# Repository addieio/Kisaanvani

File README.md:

<div align="center">

# 🌾 किसानवाणी (KisanVaani)
### *Voice-First AI Agronomist, ESP32-C6 Soil Telemetry Stake & Mandi-Direct Escrow Portal*
#### **Built for Hack with Delhi 4.0**

**Empowering smallholder Indian farmers through biophysical root-zone telemetry, edge computer-vision crop pathology, Indic-language voice AI, offline GSM feature-phone inclusion, and disintermediated fair-price mandi sales.**

---

### 🌐 Live Production Deployment
**Web Platform & Escrow Marketplace**: **[https://kisanvaani-eight.vercel.app](https://kisanvaani-eight.vercel.app)**
*Experience the live Farmer Portal, B2B Procurement Desk, Cold-Chain Logistics Calculator, and Government Sowing Quota Balancer directly in your browser.*

---

</div>

## 📖 Executive Summary & Vision

Smallholder cultivators across India face four systemic vulnerabilities:
1. **Late Crop Disease Detection**: Delayed pathology identification causes 20–40% preventable yield loss from foliar blights, rusts, and root rot.
2. **The Smartphone & Connectivity Divide**: Over 65% of rural Indian farmers do not own smartphones or operate in rural connectivity dark zones. They carry basic ₹1,000 keypad feature phones (GSM/2G) and are excluded from modern touch-screen apps.
3. **Digital Literacy & Interface Barriers**: Text-heavy dashboards alienate non-literate farmers who operate predominantly through verbal communication.
4. **Exploitative Middlemen & Credit Inaccessibility**: Middlemen depress farmgate prices, while banks (KCC loans) and insurers (PMFBY claims) require verified, tamper-proof soil and crop telemetry that farmers cannot produce.

**KisanVaani unifies five complementary engineering pillars to solve these challenges end-to-end:**
- 📡 **Real IoT Hardware Stake (Seeed Studio XIAO ESP32-C6)**: Field telemetry with Nordic UART BLE 5.0, Crowtail capacitive moisture auto-calibration, DHT22 micro-climate monitoring, MPU-6050 physical tilt detection, SSD1306 OLED with 5-second alert toasts, and Active-LOW pump relay safety cutoffs.
- 📞 **Zero-Smartphone Offline Telephony (Twilio Voice IVR + Sarvam AI Bulbul TTS)**: Enables farmers with basic keypad feature phones to verbally list crops, accept buyer bids via automated Hindi phone calls, and receive soil emergency alerts via SMS.
- 📱 **Voice-First Mobile App (Flutter & Apple iOS 18 Design)**: Large touch targets (≥74px), zero typing, 5 regional languages (Hindi, Punjabi, Marathi, Tamil, English), reactive BLE scanner, and tactile haptic feedback.
- 🔬 **Edge Computer Vision & AI Agronomist (YOLOv8 + Google Gemini 3.8 Flash)**: Custom-trained 12-class edge pathology model paired with conversational Hindi agronomy advice and spoken audio.
- 🌐 **Full-Stack Web Platform & Escrow Marketplace (Next.js 15 & Supabase on Vercel)**: Farmer portal, B2B restaurant procurement portal with radial cold-chain logistics, government district sowing quota balancer, and certified KCC/PMFBY financial passport exports.

---

## 🏛️ System Architecture

```
                                    [ Farmer / Cultivator ]
                                               │
                ┌───────────────────────────────┼───────────────────────────────┐
                ▼                               ▼                               ▼
      [ Next.js 15 Web PWA ]         [ 2G Basic Feature Phone ]         [ Flutter Android App ]
  https://kisanvaani-eight.vercel.app  (Zero Internet / Keypad GSM)      (BLE 5.0, Camera HUD, TTS)
                │                               │                               │
                │                ┌──────────────┴──────────────┐                │
                │                ▼                             ▼                │
                │      [ Twilio Voice IVR ]          [ Twilio SMS Gateway ]     │
                │   • Verbal Crop Posting (NLU)     • 4-Digit Handover Gate PIN │
                │   • Sarvam Bulbul Indic TTS       • Biophysical Soil Alarms   │
                │   • DTMF / Voice Bid Acceptance   (Hypoxia, Drought, Urea)    │
                │                └──────────────┬──────────────┘                │
                │                               │                               │
                ├───────────────────────────────┼───────────────────────────────┤
                ▼                               ▼                               ▼
    [ YOLOv8 Edge Vision ]           [ Gemini 3.8 Flash Doctor ]       [ XIAO ESP32-C6 Stake ]
    • Custom 12-Class Model          • Actionable Hindi Advice         • Crowtail Capacitive Moist
    • Trained Weights (best.pt)      • Automated Speech Generation     • DHT22 Temp & Humidity
    • Bounding Box Localization      • Voice Triage Dialog             • MPU-6050 6-DOF Tilt IMU
                │                               │                      • SSD1306 0.96" OLED Toast
                │                               │                      • Dual Active-LOW Relay Cutoff
                │                               │                               │
                └───────────────────────────────┴───────────────────────────────┘
                                                │
                                                ▼
                                [ Supabase PostgreSQL 16 ]
                       • 16 Normalized Database Tables
                       • Regional Sowing Quota Locks (Anti-Glut)
                       • Mandi-Direct Escrow (4-Digit PIN Handover)
                       • KCC Loan & PMFBY Insurance Dossier Exports
```

---

## 📡 Hardware Stake & Sensor Architecture

The physical field sensor stake monitors root-zone metrics, micro-climate factors, and physical stake stability, communicating over Nordic UART BLE 5.0:

```
                  ┌─────────────────────────────────────────────────────────┐
                  │              Seeed Studio XIAO ESP32-C6                 │
                  │             (RISC-V 160MHz, BLE 5.0, Wi-Fi 6)           │
                  └──────┬────────────┬───────────┬────────────┬────────────┘
                         │            │           │            │
            Analog ADC1  │   1-Wire   │    I2C    │    GPIO    │ Dual GPIO
               (D1/GPIO1)│  (D2/GPIO2)│ (D4/D5)   │ (D8/GPIO19)│ (D9/GPIO20 & D10/GPIO9)
                         ▼            ▼           ▼            ▼            ▼
                  ┌────────────┐ ┌─────────┐ ┌─────────┐ ┌──────────┐ ┌────────────────┐
                  │  Crowtail  │ │  DHT22  │ │ SSD1306 │ │Active-Low│ │Optocoupled Dual│
                  │ Capacitive │ │Temp/Hum │ │  OLED   │ │  Buzzer  │ │Relay Motor Cut │
                  │  Moisture  │ │ Sensor  │ │ Display │ │(Acoustic)│ │ (Songle 10A)   │
                  └────────────┘ └─────────┘ └────┬────┘ └──────────┘ └────────────────┘
                                                  │
                                                  ▼
                                             ┌─────────┐
                                             │MPU-6050 │
                                             │6-DOF IMU│
                                             │ (Tilt)  │
                                             └─────────┘
```

### 1. What All Sensors Are There & How Each Works

#### 🌾 A. Crowtail Capacitive Soil Moisture Sensor (v2.0)
* **Hardware Interfacing**: Analog Pin `D1` / `GPIO 1` (`ADC1_CH1`).
* **Working Principle**: Operates on the principle of **dielectric permittivity** of soil. Unlike cheap resistive probes that corrode rapidly through electrolysis, the capacitive design uses insulated copper traces on a PCB forming a capacitor whose dielectric medium is the surrounding soil and moisture. Water has a high dielectric constant ($\approx 80$) compared to dry soil ($\approx 3\text{--}5$) and air ($\approx 1$).
* **Signal Processing & Auto-Calibration**: As volumetric water content rises, capacitance increases, lowering the timer output voltage. The firmware captures 12-bit ADC values ($0\text{--}4095$) with multi-sample rolling average smoothing, dynamically calibrating the dry-air baseline ($\approx 2800\text{--}3100$ raw ADC) and saturation threshold ($\approx 1200\text{--}1400$ raw ADC) into a calibrated $0\text{--}100\%$ Volumetric Soil Moisture metric.
* **Root Hypoxia Emergency Action**: When moisture exceeds $80\%$ (waterlogging / anaerobic root suffocation danger), the stake triggers an instant hardware pump cutoff, emits acoustic siren pulses, and flashes an OLED alert.

#### 🌡️ B. DHT22 (AM2302) Digital Temperature & Relative Humidity Sensor
* **Hardware Interfacing**: Digital Pin `D2` / `GPIO 2` with an external $10\text{ k}\Omega$ pull-up resistor to $3.3\text{V}$.
* **Working Principle**: Uses a capacitive humidity sensing element and a high-precision Negative Temperature Coefficient (NTC) thermistor. An onboard 8-bit chip outputs calibrated digital signals over a proprietary single-bus 1-wire protocol.
* **Biophysical Role & Vapor Pressure Deficit (VPD)**: Accurately tracks micro-climate conditions around the crop canopy ($-40^\circ\text{C}$ to $+80^\circ\text{C} \pm 0.5^\circ\text{C}$; $0\text{--}100\%$ RH $\pm 2\%$). Combined temperature and relative humidity allow real-time computation of **Vapor Pressure Deficit (VPD)**. When humidity remains $>90\%$ in warm temperatures, the biophysical engine predicts fungal spore germination (e.g., powdery mildew, leaf spot) before physical symptoms appear on leaves.

#### 📐 C. MPU-6050 6-Axis Motion Tracking Sensor (Accelerometer + Gyroscope)
* **Hardware Interfacing**: I2C Bus via `GPIO 22` (`SDA` / `D4`) and `GPIO 23` (`SCL` / `D5`) at $400\text{kHz}$ Fast Mode (I2C address `0x68`).
* **Working Principle**: Integrates a 3-axis MEMS accelerometer with a 3-axis MEMS gyroscope and an internal Digital Motion Processor (DMP).
* **Physical Telemetry Role**: Continuously monitors the physical inclination and spatial orientation of the field sensor stake. Detects physical displacement, stake toppling by high winds, heavy rain soil washouts, or cattle disturbances. If inclination exceeds $25^\circ$ from the vertical normal, the firmware flags a `STAKE_DISPLACED` status to alert the farmer that root-zone readings may no longer be accurate.

#### 📺 D. 0.96" SSD1306 Monochrome OLED Display (128x64 Pixels)
* **Hardware Interfacing**: Shared I2C Bus (`GPIO 22` SDA, `GPIO 23` SCL, I2C address `0x3C`).
* **Working Principle**: High-contrast self-emissive organic light-emitting diode matrix with zero backlight bleed, readable under harsh direct sunlight in the field.
* **Visual Layout & Toast Alert System**:
  - **Telemetry Carousel**: Cycles between real-time moisture %, temperature, humidity, NPK status, and pump relay states.
  - **Custom Compact Hindi Bitmaps**: Displays native Hindi text and icons (*नमी*, *मौसम*, *सिंचाई*, *उचित*, *सूखी*) without requiring external font flash overhead.
  - **5-Second Double-Border Toast System**: When app sliders or remote simulation commands are dispatched, an interruptible double-bordered alert card overrides the screen for exactly $5,000\text{ms}$ with beep tones, showing the updated parameter before restoring live metrics.

#### 🔊 E. Active-Low Acoustic Electromagnetic Buzzer (12mm)
* **Hardware Interfacing**: Digital Pin `D8` / `GPIO 19`.
* **Working Principle**: Built-in oscillation circuit driven by a low-side NPN/MOSFET switch. Pulling `GPIO 19` `LOW` activates the internal oscillator, driving the diaphragm at $\approx 2.7\text{kHz}$.
* **Acoustic Feedback Modes**: Provides distinct auditory feedback for rural field conditions: single short chirp ($100\text{ms}$) for button click / BLE command reception; triple rapid pulse ($3\times 80\text{ms}$) for threshold warnings; continuous pulsed siren for emergency over-irrigation pump cutoff.

#### ⚡ F. Dual-Pin Optocoupled Active-LOW Power Relay (Songle SRD-05VDC-SL-C)
* **Hardware Interfacing**: Driven in parallel by Digital Pin `D9` / `GPIO 20` (Primary) and Digital Pin `D10` / `GPIO 9` (Secondary) for pin fault tolerance and high switching reliability.
* **Working Principle**: Employs an EL817 optocoupler for complete galvanic isolation between the low-voltage ESP32 logic rail ($3.3\text{V}$) and high-power motor/pump circuits (up to $250\text{V AC} / 10\text{A}$ or $30\text{V DC} / 10\text{A}$). Pulling the control pins `LOW` illuminates the internal infrared LED, saturating the phototransistor and energizing the $5\text{V}$ relay coil.
* **Fail-Safe Protection**: Defaults to `HIGH` (Normally Open / de-energized) on reboot, power brownout, or high moisture ($>80\%$) to prevent field flooding.

---

### 2. Complete Hardware Circuit & Pinout Table

| Component | XIAO ESP32-C6 Pin | GPIO | Protocol / Mode | Connection Details |
| :--- | :--- | :--- | :--- | :--- |
| **Relay Signal (IN)** | **D9** *(Primary)* | **GPIO 20** | Digital Output | Active-LOW ($0\text{V}$ activates coil, turns motor ON) |
| **Relay Signal (ALT)** | **D10** *(Secondary)* | **GPIO 9** | Digital Output | Driven in parallel with D9 for pin fault tolerance |
| **Relay VCC** | **5V** | 5V Rail | Power | Connect to 5V rail (USB / external supply) |
| **Relay GND** | **GND** | GND | Ground | Common ground rail |
| **SSD1306 OLED SDA** | **D4** | **GPIO 22** | I2C Data (`0x3C`) | Display data line |
| **SSD1306 OLED SCL** | **D5** | **GPIO 23** | I2C Clock | Display clock line |
| **DHT22 Temp/Humidity** | **D2** | **GPIO 2** | Digital 1-Wire | $10\text{ k}\Omega$ pull-up resistor to 3.3V |
| **Crowtail Moisture Sensor** | **D1** *(or D0)* | **GPIO 1** | Analog ADC1_CH1 | Capacitive soil moisture signal |
| **Active-Low Buzzer** | **D8** | **GPIO 19** | Digital Output | Active-LOW acoustic buzzer driver |
| **MPU-6050 Accelerometer** | **D4 (SDA) / D5 (SCL)** | **GPIO 22 / 23** | I2C (`0x68`) | 6-DOF stake tilt & displacement detection |
| **Hardware Mode Button** | **D3** | **GPIO 21** | Digital Input | Pull-up to 3.3V, momentary to GND |

---

## ⚙️ How the Entire System Works (End-to-End Mechanics)

### 1. Root-Zone Biophysical Telemetry & BLE 5.0 Broadcast
1. The **XIAO ESP32-C6** reads analog moisture from the Crowtail sensor, digital ambient climate from the DHT22, and physical orientation angles from the MPU-6050.
2. An onboard biophysical engine computes rolling averages, checks threshold limits, and updates the **SSD1306 OLED**.
3. Telemetry is serialized into a compact string format (`TELEM:moist,temp,hum,pump`) and broadcast via the **Nordic UART Service (NUS)**:
   - **Service UUID**: `6E400001-B5A3-F393-E0A9-E50E24DCCA9E`
   - **RX Characteristic (Write)**: `6E400002-B5A3-F393-E0A9-E50E24DCCA9E`
   - **TX Characteristic (Notify)**: `6E400003-B5A3-F393-E0A9-E50E24DCCA9E`
4. The **Flutter Mobile App** or **Web Bluetooth Bridge** subscribes to notifications, synchronizing real-time field status with zero manual polling.

---

### 2. 📞 Zero-Smartphone Offline Engine (Twilio Voice IVR + Sarvam AI Bulbul TTS)

Farmers in remote rural areas with basic ₹1,000 keypad feature phones (GSM/2G) participate in the digital marketplace without needing smartphones or mobile internet:

#### 🎙️ Workflow A: Verbal Crop Listing via Phone Call (No Internet Required)
1. **Interactive Voice IVR**: Farmer dials the platform hotline (or receives an automated check-in call) via Twilio Voice (`/api/twilio/offline-listing/voice`).
2. **Spoken Hindi Guidance**: The system greets the farmer:
   > *"नमस्ते किसान भाई! किसानवाणी में आपका स्वागत है। आप कौन सी सब्जी या फसल का आर्डर पोस्ट करना चाहते हैं और कितनी मात्रा? जैसे बोलिए: 300 किलो टमाटर। बीप के बाद अपनी आवाज में बोलें।"*
3. **Dialect-Agnostic Speech Capture**: Farmer speaks naturally into their phone (e.g., *"300 किलो टमाटर 40 रुपये भाव"* or *"5 क्विंटल आलू"*).
4. **AI Speech NLU Extraction (Gemini 3.8 Flash + Regex Classifier)**:
   - **Commodity Identification**: Extracts colloquial names (*tamatar*, *aloo*, *pyaz*, *mirch*, *bhindi*) into standardized market listings.
   - **Quantity Parsing**: Understands both kilograms (*किलो*) and quintals (*क्विंटल* = 100 kg).
   - **Target Rate**: Detects spoken rates per kg.
5. **Instant Database Sync**: Produce is published live to the Supabase database (`listings` table) tagged as `OFFLINE_VOICE_POST` and displayed on the buyer portal.

#### 🤝 Workflow B: Order Acceptance via Automated Hindi Calls (Sarvam AI Bulbul TTS)
1. **Outbound Call Trigger**: When a buyer places an order on the marketplace, an automated call is dispatched to the farmer via Twilio REST API.
2. **Sarvam AI Bulbul TTS (`bulbul:v4-flash`)**:
   - Synthesizes telecom-standard **8000Hz WAV audio** with natural Hindi phrasing:
     > *"नमस्कार जी। आपके लिए एक नया ऑर्डर आया है। देसी लाल टमाटर, 300 किलो, कुल राशि 12,000 रुपये। ऑर्डर स्वीकार करने के लिए कृपया एक दबाएं। या हाँ बोलें।"*
   - **Zero-Latency In-Memory Audio Pre-Warming**: Buffers pre-rendered audio during checkout, streaming in **<15ms** without stutter.
3. **Dual Acceptance (DTMF or Voice)**:
   - **Keypad**: Press **`1`** (DTMF tone detection).
   - **Voice**: Speak affirmative words: *"हाँ"*, *"स्वीकार"*, *"मंजूर"*, *"ठीक"*, *"done"*.
4. **State Transition**: Order transitions from `BID` ➔ `ACCEPTED`.

#### 📩 Workflow C: 4-Digit Handover Gate PIN & SMS Alerts
1. **Cryptographic Escrow PIN**: An SMS sends the farmer a unique **4-digit Gate PIN** (`4829`). When cold-chain transport arrives at the farmgate, the driver enters this PIN in the portal to release escrow funds.
2. **Biophysical Soil Alarms**: Real-time SMS alerts dispatched when field sensors detect stress conditions:
   - 🌊 **Waterlogging / Root Hypoxia**: *जलभराव! खेत में नमी अधिक है, मोटर तुरंत बंद करें।*
   - ☀️ **Severe Drought**: *सूखा तनाव! खेत में नमी कम है, तुरंत सिंचाई करें।*
   - ⚠️ **Excess Urea / Toxicity**: *अत्यधिक नाइट्रोजन! रासायनिक खाद तुरंत रोक दें।*
   - 🍂 **Nitrogen Starvation**: *नाइट्रोजन कमी! यूरिया या जीवामृत का छिड़काव करें।*
   - 🔒 **Phosphorus Lock**: *फास्फोरस कमी! जड़ विकास हेतु डीएपी या SSP खाद दें।*
   - 🥀 **Potassium Deficit**: *पोटाश कमी! फल चमक व मिठास हेतु 00:00:50 छिड़कें।*

---

### 3. 📱 Voice-First Mobile Application (Flutter 3.29)
* **Touch Ergonomics**: All actionable buttons are $\ge 74\text{px}$ in height with heavy haptic feedback (`HapticFeedback.heavyImpact()`).
* **5 Regional Indian Languages**: Hindi (हिंदी), Punjabi (ਪੰਜਾਬੀ), Marathi (मराठी), Tamil (தமிழ்), English (Indian).
* **Nordic UART BLE Controller**:
  - Real-time reactive scanning sheet using `StreamBuilder<List<ScanResult>>`.
  - Android system bonded & connected device support (`FlutterBluePlus.bondedDevices`).
  - 1-Tap Fast Auto-Connect (`⚡ KRISHI-AGRO-C6 से तुरंत जोड़ें`).
  - Persistent BLE Status Pill in the top navigation bar across all tabs (`C6 जुड़ा ✓` / `जोड़ें`).
* **Interactive Soil Simulator**:
  - Live sliders for Soil Moisture ($0\text{--}100\%$), Nitrogen ($0\text{--}200\text{ mg/kg}$), Phosphorus ($0\text{--}150\text{ mg/kg}$), and Potassium ($0\text{--}300\text{ mg/kg}$).
  - Adjusting sliders sends `SET:MOIST=` and `SET:NPK=` over BLE, triggering 5-second alert toasts on the physical OLED and buzzer beeps.
* **YOLO Leaf Camera Scanner**:
  - Live camera HUD with targeting reticle for diseased crop leaves.

---

### 4. 🔬 Edge Computer Vision (YOLOv8) & Gemini 3.8 Flash Agronomist
* **Custom YOLOv8 Model (`detection/best (1).pt`)**:
  - Trained specifically on 12 agricultural pathology classes:
    `ALS`, `Angular Leafspot`, `Anthracnose Fruit Rot`, `Bean Rust`, `Blossom Blight`, `Gray Mold`, `Leaf Spot`, `Powdery Mildew Fruit`, `Powdery Mildew Leaf`, `disease`, `leaf mold`, `spider mites`.
  - Real-time bounding box localization and confidence score evaluation.
* **Government-Subsidized Curative Remedies**:
  - Provides active chemical/organic ingredient, dilution ratio per 15L backpack pump, and government-mandated MRP price caps.
* **Gemini 3.8 Flash Conversational Agronomist**:
  - Delivers concise, conversational 2–3 sentence Hindi remedies with automated spoken text-to-speech.

---

### 5. 🌐 Full-Stack Web Platform & Fair-Price Escrow Marketplace
**Hosted on Vercel at: [https://kisanvaani-eight.vercel.app](https://kisanvaani-eight.vercel.app)**

* **Farmer Portal (`/farmer`)**:
  - Live biophysics dashboard, weather forecasts, regional anti-glut crop planning, and produce listing.
* **Explore Crops & Fertilizer Network (`/farmer/crops`)**:
  - Matches optimal crops to current soil NPK and moisture levels with a step-by-step fertilizer plan and nearby verified agro-dealer inventory with direct calling.
* **B2B Buyer / Restaurant Procurement Portal (`/buyer`)**:
  - Real-time inventory browsing, bulk order placement, multi-ring radial cold-chain logistics routing (R1 <80km, R2 80–300km, R3 >300km), transit temperature monitoring, and escrow release with 4-digit PIN verification.
* **Government District Portal (`/govt`)**:
  - Regional crop sowing quota balancer with traffic-light status (Green/Amber/Red) to prevent harvest gluts and catastrophic price crashes.
* **Financial Passport Exports**:
  - **KCC Bank Loan Telemetry Passport**: Certified soil health, irrigation history, and NPK stability record for bank credit officers.
  - **PMFBY Crop Insurance Loss Dossier**: Tamper-proof telemetry audit log proving waterlogging or drought events for fast-track insurance claim settlement.
  - Complete timestamped CSV ledger export.

---

## 🗄️ Supabase Database Architecture (16 Normalized Tables)

| Table | Description |
| :--- | :--- |
| `farmers` | Farmer registration, phone number, district, GPS coordinates, preferred language. |
| `plots` | Farm acreage, soil classification, active crop, GIS polygon boundaries. |
| `sowing_locks` | Quota Balancer: regional crop ceiling status (`GREEN`, `AMBER`, `RED`). |
| `buyer_preorders` | Forward contracts from institutional cloud kitchens and dark stores. |
| `sensor_readings` | ESP32 telemetry: Moisture %, Temperature, Humidity, N, P, K, pH, pump relay state. |
| `alerts` | Dynamic biophysical alerts with multilingual spoken text (`hi`, `pa`, `mr`, `ta`, `en`). |
| `dealers` | Verified local agro-dealers and distance calculations. |
| `remedies` | Recommended chemical & organic curative steps with government MRP price caps. |
| `dealer_leads` | Agro-dealer lead tracking and referral monetization log. |
| `listings` | Active marketplace crop listings, quality scores, and verification PINs. |
| `bids` | Buyer bids and procurement offers. |
| `orders` | Escrow state machine: `BID` ➔ `ACCEPTED` ➔ `IN_TRANSIT` ➔ `HANDOVER` ➔ `PAID`. |
| `order_events` | Immutable audit log of all order events and SMS/IVR notifications. |
| `farm_diary` | Immutable sensor diary for crop insurance proof. |
| `insurance_claims` | PMFBY insurance claims, evidence dossier URLs, and approval status. |
| `logistics_routes` | Radial delivery clusters (<80km, 80–300km, >300km) and transport costs. |

---

## 🏆 Hack with Delhi 4.0 Alignment

| Judging Category | KisanVaani Implementation |
| :--- | :--- |
| **Real-World Inclusivity & Impact** | Leaves no cultivator behind. Farmers with basic ₹1,000 keypad feature phones and zero mobile data can verbally list produce, accept buyer orders over automated Hindi phone calls, and receive biophysical alerts via **Sarvam AI & Twilio Voice/SMS**. |
| **Technical Depth & Integration** | Spans 5 distinct engineering layers: Next.js 15 PWA on Vercel, Flutter 3.29, YOLOv8 Edge Vision, Gemini 3.8 Flash NLU, Sarvam AI Bulbul TTS, Twilio Voice IVR & SMS, ESP32-C6 BLE 5.0 Hardware, and Supabase PostgreSQL 16. |
| **AI Innovation** | Domain-specific prompt engineering with Gemini 3.8 Flash, custom-trained 12-class edge computer vision on leaf pathologies, and Sarvam AI natural Indic Hindi speech synthesis with in-memory audio pre-warming (<15ms). |
| **Hardware & IoT Engineering** | Physical Seeed Studio XIAO ESP32-C6 stake with Nordic UART BLE 5.0, Crowtail capacitive moisture auto-calibration, DHT22 micro-climate monitoring, MPU-6050 physical tilt detection, dual-pin Active-LOW pump relay, 5-second OLED toast overlays, and automated safety cutoffs based on mathematical root hypoxia models. |
| **UI/UX Aesthetics & Accessibility** | Apple iOS 18 Design guidelines tailored for rural farmers with $\ge 74\text{px}$ touch ergonomics, high-contrast visual cues, tactile haptics, and zero-typing telephony accessibility. |

---

## 📜 License

Distributed under the MIT License. Built with ❤️ for Indian smallholder farmers.

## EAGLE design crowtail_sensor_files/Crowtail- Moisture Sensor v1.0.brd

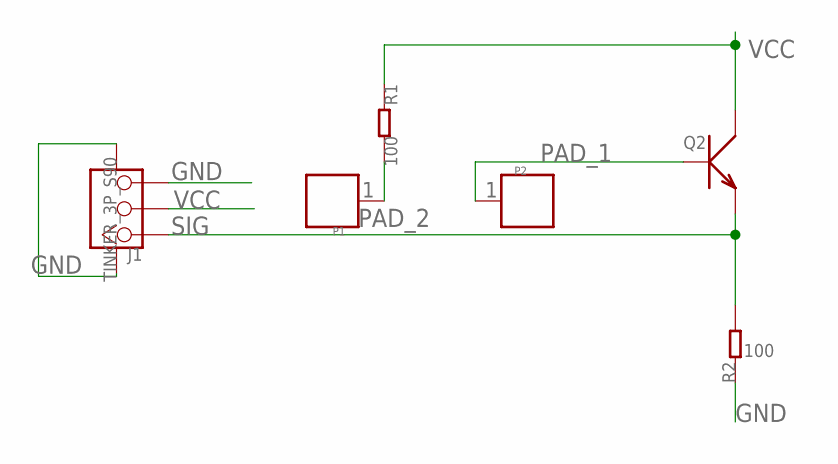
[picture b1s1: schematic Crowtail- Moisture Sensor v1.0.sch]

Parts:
J1: TINKER_3P_S90
P1, P2: PAD.03; 1P-SMD-0.76X0.76
Q2: TRANSISTOR-NPN-SOT23''; SOT23
R1, R2: 100; 0603

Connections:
GND: J1.3, J1.SS1, J1.SS2, R2.1
PAD_1: P2.1, Q2.1 (B)
PAD_2: P1.1, R1.2
SIG: J1.1, Q2.2 (E), R2.2
VCC: J1.2, Q2.3 (C), R1.1

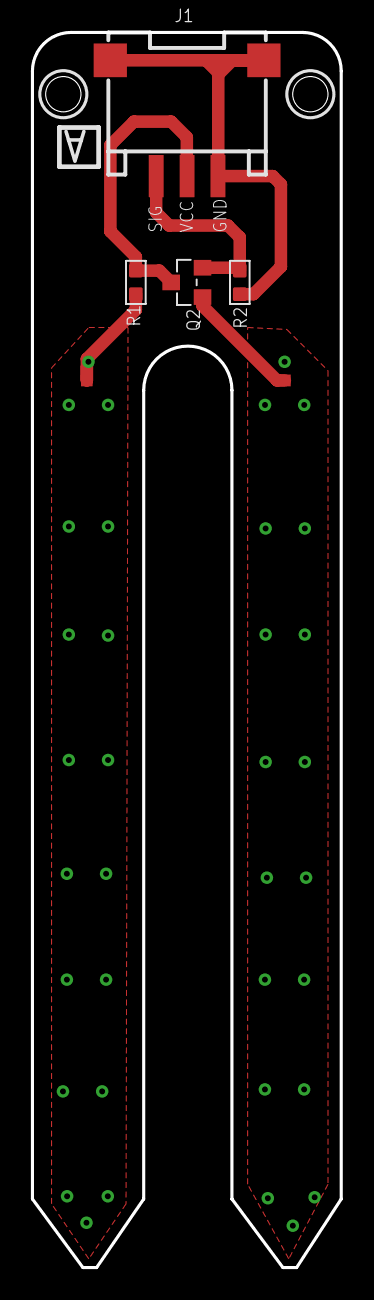
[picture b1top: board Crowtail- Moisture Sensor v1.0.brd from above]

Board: 2 copper layers, 20.0 x 80.0 mm, 6 parts (0 on the bottom side), 5 nets.
